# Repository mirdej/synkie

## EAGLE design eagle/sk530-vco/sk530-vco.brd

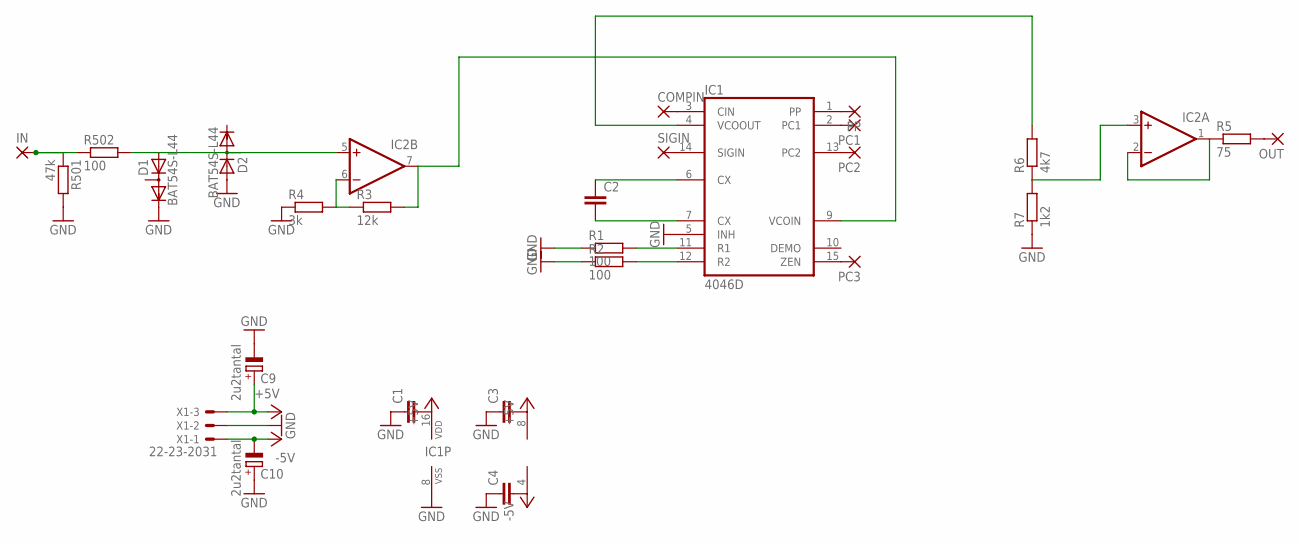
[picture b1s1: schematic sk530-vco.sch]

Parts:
C1, C2, C3, C4: C-EUC1206; C1206
C9, C10: 2u2tantal; CT3528
COMPIN: 3,17/1,1
D1, D2: BAT54S-L44; SOT23
IC1: 4046D; SO16
IC2: DUAL_OPAMPD; SO08
IN: 3,17/1,1
OUT: 3,17/1,1
PC1, PC2, PC3: 3,17/1,1
PP: 3,17/1,1
R1, R2, R502: 100; R1206
R3: 12k; R1206
R4: 3k; R1206
R5: 75; R1206
R6: 4k7; R1206
R7: 1k2; R1206
R501: 47k; R1206
SIGIN: 3,17/1,1
X1: 22-23-2031

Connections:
+5V: C1.2, C3.2, C9.+, IC1.16 (VDD), IC2.8 (V+), X1.3
-5V: C4.2, C10.-, IC2.4 (V-), X1.1
GND: C1.1, C3.1, C4.1, C9.-, C10.+, D1.2 (C), D2.1 (A), IC1.5 (INH), IC1.8 (VSS), R1.1, R2.1, R4.1, R7.1, R501.2, X1.2
unnamed: IC1.2 (PC1), PC1.1
unnamed: OUT.1, R5.2
unnamed: IC1.1 (PP), PP.1
unnamed: IC1.13 (PC2), PC2.1
unnamed: IC1.15 (ZEN), PC3.1
unnamed: IC1.14 (SIGIN), SIGIN.1
unnamed: COMPIN.1, IC1.3 (CIN)
unnamed: C2.1, IC1.6 (CX)
unnamed: C2.2, IC1.7 (CX)
unnamed: IN.1, R501.1, R502.1
unnamed: D1.1 (A), D2.3 (AC), IC2.5 (+IN), R502.2
unnamed: IC1.11 (R1), R1.2
unnamed: IC1.12 (R2), R2.2
unnamed: IC2.6 (-IN), R3.1, R4.2
unnamed: IC1.9 (VCOIN), IC2.7 (OUT), R3.2
unnamed: IC2.1 (OUT), IC2.2 (-IN), R5.1
unnamed: IC1.4 (VCOOUT), R6.2
unnamed: IC2.3 (+IN), R6.1, R7.2

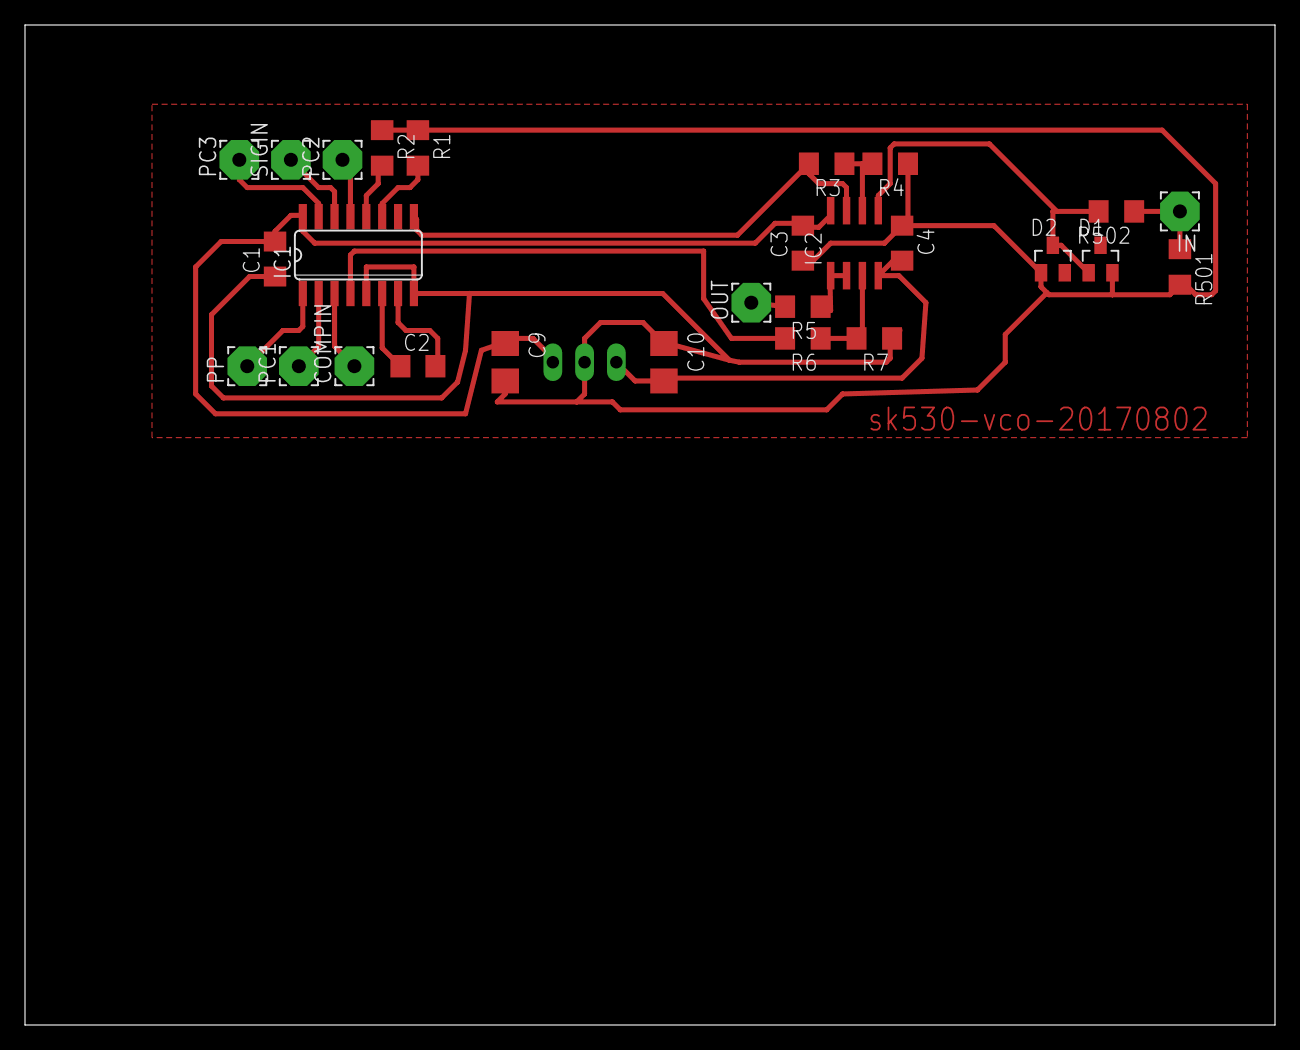
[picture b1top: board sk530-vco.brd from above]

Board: 2 copper layers, 100.0 x 80.0 mm, 28 parts (1 on the bottom side), 21 nets.

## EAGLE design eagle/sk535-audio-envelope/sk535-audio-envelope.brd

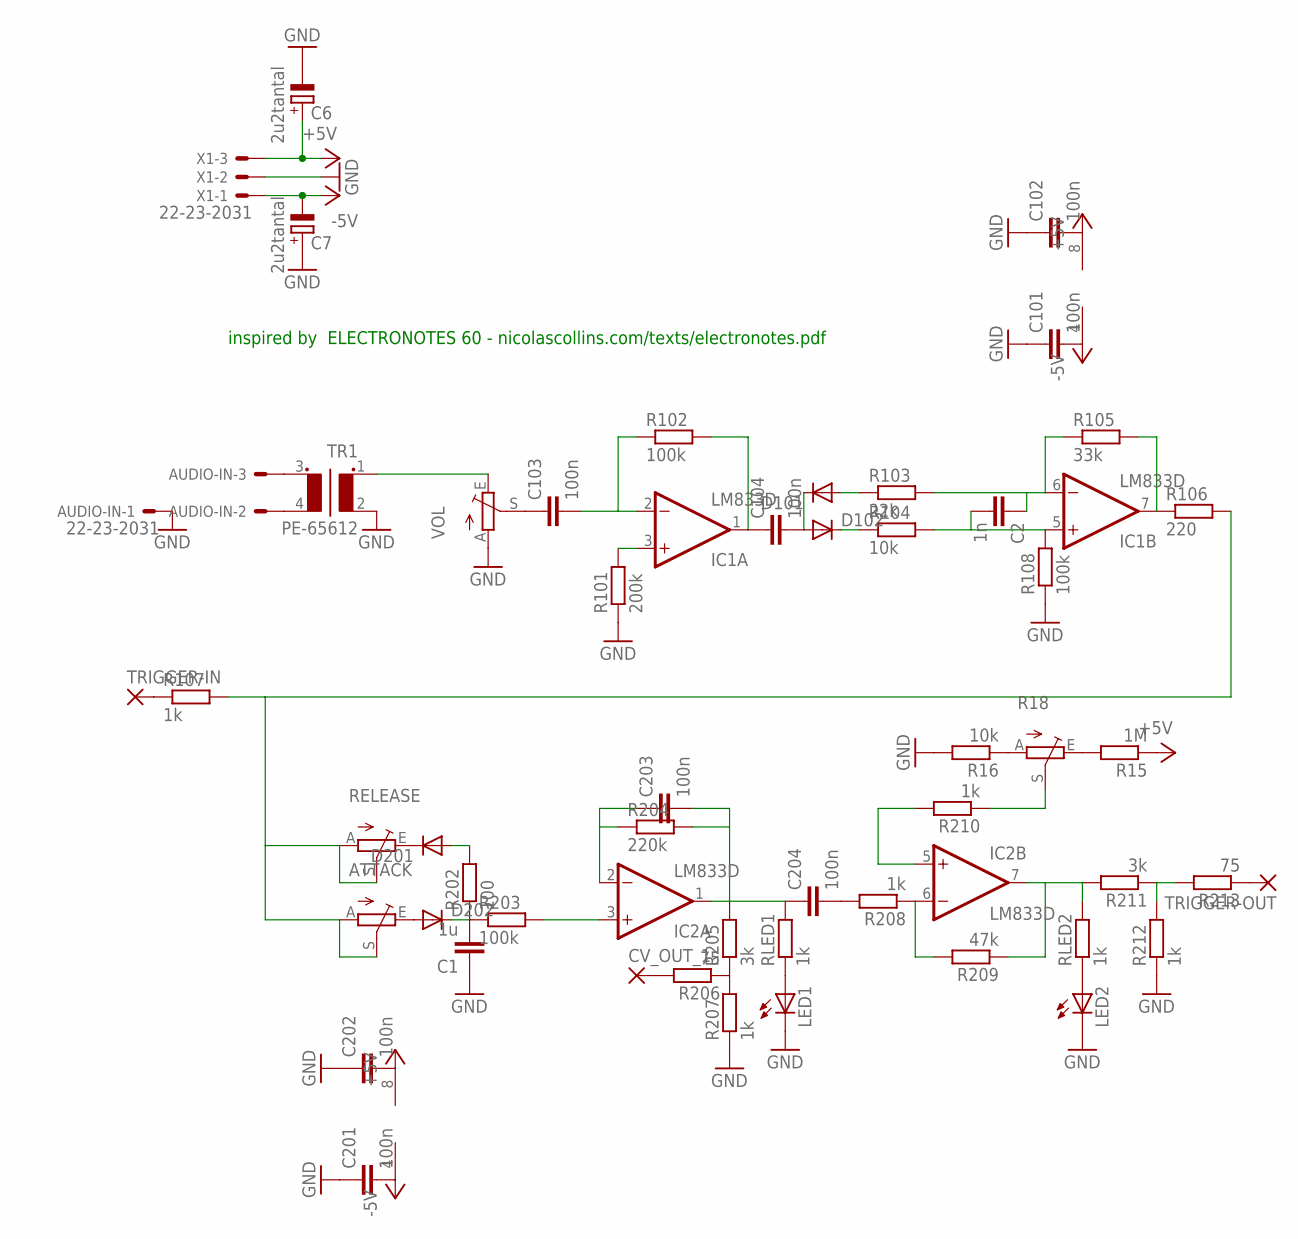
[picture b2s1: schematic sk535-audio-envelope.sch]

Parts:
ATTACK: TRIM_EU-CIP20C-4MM; CIP20C-4MM
AUDIO-IN: 22-23-2031
C1: 1u; C1206
C2: 1n; C1206
C6, C7: 2u2tantal; CT3528
C101, C102, C103, C104, C201, C202, C203, C204: 100n; C1206
CV_OUT_1: 3,17/1,1
D101, D102, D201, D202: DIODE-MINIMELF; MINIMELF
IC1, IC2: LM833D; SO08
LED1, LED2: LED3MM
R15: 1M; R1206
R16, R104: 10k; R1206
R18: TRIM_EU-CIP20C-4MM; CIP20C-4MM
R101: 200k; R1206
R102, R108, R203: 100k; R1206
R103: 22k; R1206
R105: 33k; R1206
R106: 220; R1206
R107, R207, R208, R210, R212: 1k; R1206
R202: 100; R1206
R204: 220k; R1206
R205, R211: 3k; R1206
R206, R213: 75; R1206
R209: 47k; R1206
RELEASE: TRIM_EU-CIP20C-4MM; CIP20C-4MM
RLED1, RLED2: 1k; R1206
TR1: PE-65612
TRIGGER-IN: 3,17/1,1
TRIGGER-OUT: 3,17/1,1
VOL: TRIM_EU-CIP20C-4MM; CIP20C-4MM
X1: 22-23-2031

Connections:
+5V: C6.+, C102.2, C202.2, IC1.8 (V+), IC2.8 (V+), R15.1, X1.3
-5V: C7.-, C101.2, C201.2, IC1.4 (V-), IC2.4 (V-), X1.1
GND: AUDIO-IN.1, C1.1, C6.-, C7.+, C101.1, C102.1, C201.1, C202.1, LED1.K (C), LED2.K (C), R16.2, R101.1, R108.1, R207.1, R212.1, TR1.2, VOL.A, X1.2
unnamed: TR1.1, VOL.E
unnamed: C103.1, VOL.S
unnamed: C103.2, IC1.2 (-IN), R102.1
unnamed: C104.1, IC1.1 (OUT), R102.2
unnamed: IC1.3 (+IN), R101.2
unnamed: C104.2, D101.C, D102.A
unnamed: D102.C, R104.1
unnamed: C2.2, IC1.5 (+IN), R104.2, R108.2
unnamed: C2.1, IC1.6 (-IN), R103.2, R105.1
unnamed: D101.A, R103.1
unnamed: IC1.7 (OUT), R105.2, R106.1
unnamed: R107.1, TRIGGER-IN.1
unnamed: D201.C, RELEASE.E
unnamed: D201.A, R202.2
unnamed: ATTACK.E, D202.A
unnamed: ATTACK.A, ATTACK.S, R106.2, R107.2, RELEASE.A, RELEASE.S
unnamed: C1.2, D202.C, R202.1, R203.1
unnamed: IC2.3 (+IN), R203.2
unnamed: AUDIO-IN.3, TR1.3 (S1)
unnamed: AUDIO-IN.2, TR1.4 (S2)
unnamed: C203.1, IC2.2 (-IN), R204.1
unnamed: C203.2, C204.1, IC2.1 (OUT), R204.2, R205.2, RLED1.2
unnamed: R205.1, R206.1, R207.2
unnamed: LED1.A, RLED1.1
unnamed: C204.2, R208.2
unnamed: IC2.6 (-IN), R208.1, R209.2
unnamed: IC2.7 (OUT), R209.1, R211.2, RLED2.2
unnamed: R15.2, R18.E
unnamed: R16.1, R18.A
unnamed: R18.S, R210.1
unnamed: IC2.5 (+IN), R210.2
unnamed: LED2.A, RLED2.1
unnamed: R213.1, TRIGGER-OUT.1
unnamed: R211.1, R212.2, R213.2
unnamed: CV_OUT_1.1, R206.2

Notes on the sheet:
inspired by ELECTRONOTES 60 - nicolascollins.com/texts/electronotes.pdf

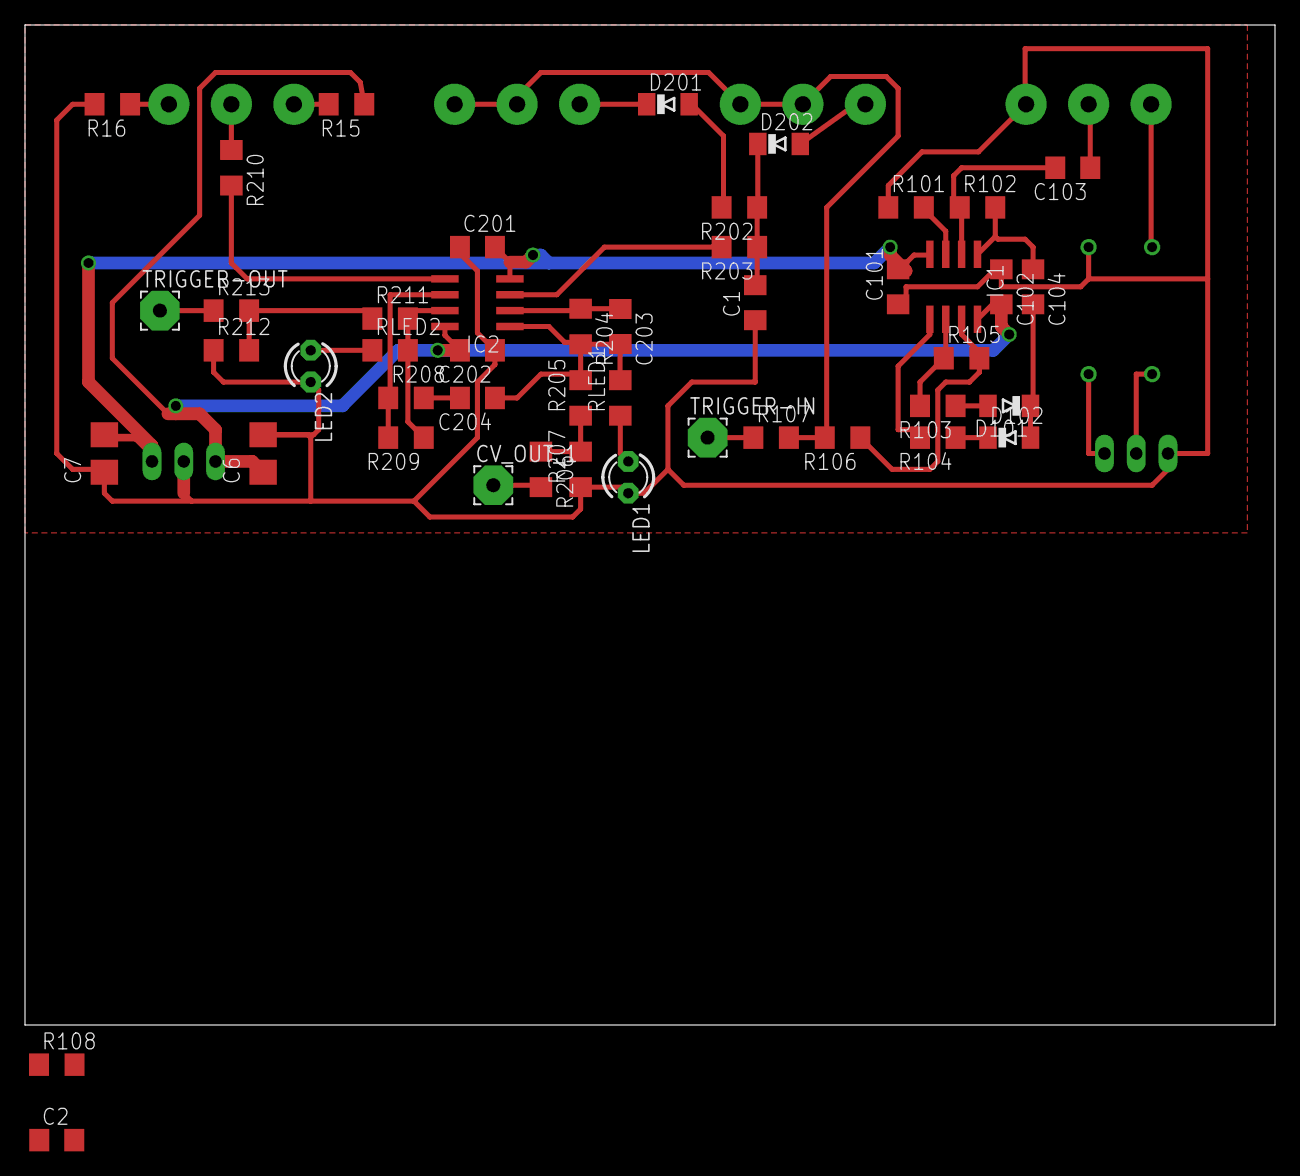
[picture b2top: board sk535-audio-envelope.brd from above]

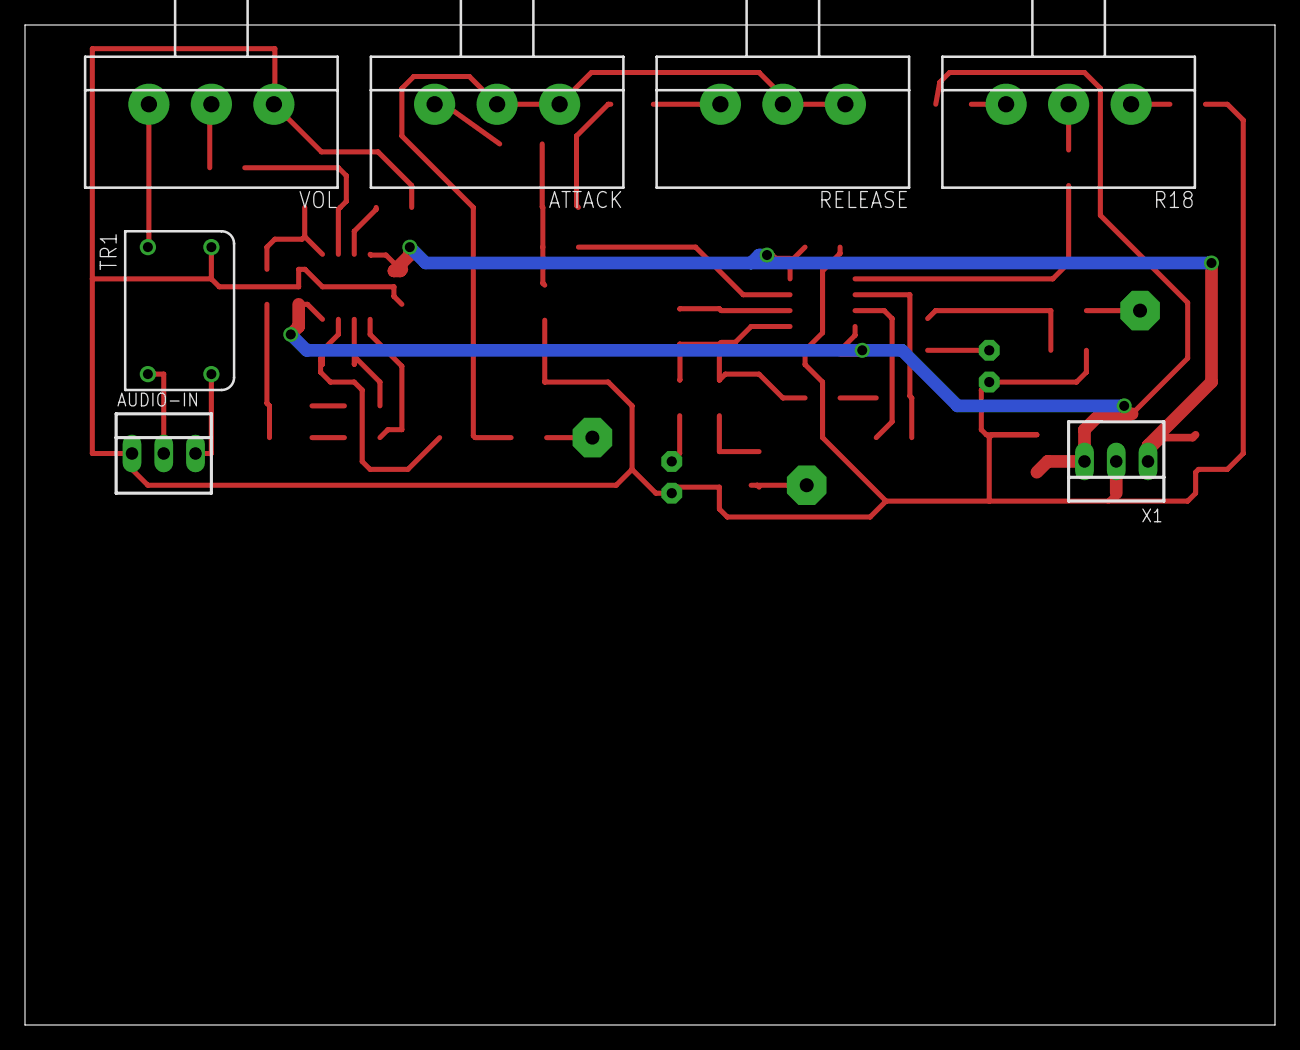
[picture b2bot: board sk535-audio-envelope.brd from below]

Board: 2 copper layers, 100.0 x 80.0 mm, 54 parts (7 on the bottom side), 38 nets.

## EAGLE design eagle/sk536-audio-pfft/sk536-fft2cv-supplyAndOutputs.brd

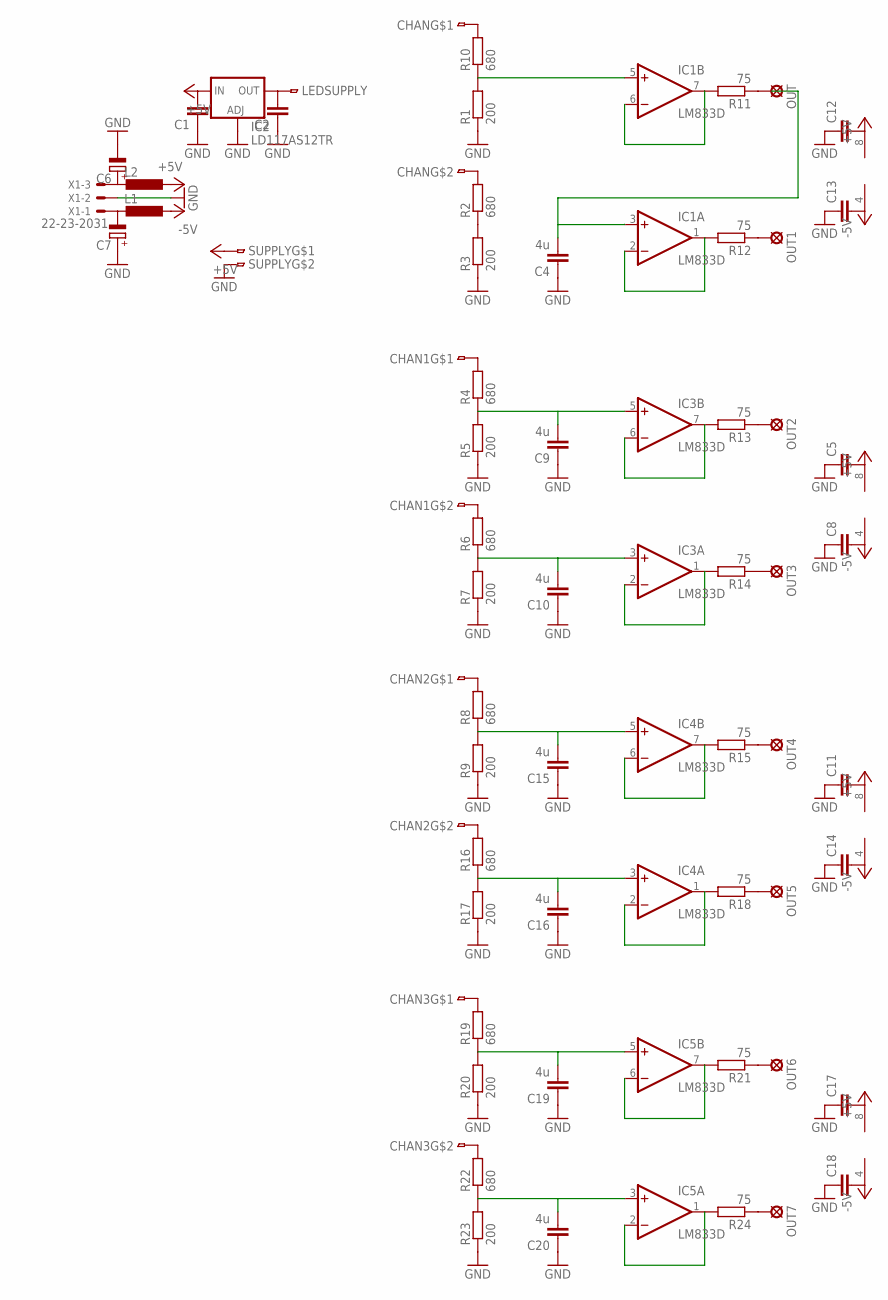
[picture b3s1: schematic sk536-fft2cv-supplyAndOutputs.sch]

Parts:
C1, C2, C5, C8, C11, C12, C13, C14, C17, C18: C-EUC0603; C0603
C4, C9, C10, C15, C16, C19, C20: 4u; C1206
C6, C7: CPOL-EUCT3528; CT3528
CHAN, CHAN1, CHAN2, CHAN3: 2PIN-SMD-2.54
IC1, IC3, IC4, IC5: LM833D; SO08
IC2: LD117AS12TR; SOT223
L1, L2: L-EUL2012C; L2012C
LEDSUPPLY: 1PINSMD
OUT, OUT1, OUT2, OUT3, OUT4, OUT5, OUT6, OUT7: LSP13
R1, R3, R5, R7, R9, R17, R20, R23: 200; R1206
R2, R4, R6, R8, R10, R16, R19, R22: 680; R1206
R11, R12, R13, R14, R15, R18, R21, R24: 75; R1206
SUPPLY: 2PIN-SMD-2.54
X1: 22-23-2031

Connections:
+5V: C1.2, C5.2, C11.2, C12.2, C17.2, IC1.8 (V+), IC2.3 (IN), IC3.8 (V+), IC4.8 (V+), IC5.8 (V+), L2.1, SUPPLY.2
-5V: C8.2, C13.2, C14.2, C18.2, IC1.4 (V-), IC3.4 (V-), IC4.4 (V-), IC5.4 (V-), L1.1
GND: C1.1, C2.1, C4.1, C5.1, C6.-, C7.+, C8.1, C9.1, C10.1, C11.1, C12.1, C13.1, C14.1, C15.1, C16.1, C17.1, C18.1, C19.1, C20.1, IC2.1 (ADJ), R1.1, R3.1, R5.1, R7.1, R9.1, R17.1, R20.1, R23.1, SUPPLY.3, X1.2
unnamed: CHAN.2, R10.2
unnamed: C2.2, IC2.4 (OUT), LEDSUPPLY.2
unnamed: OUT.MP, R11.1
unnamed: IC1.5 (+IN), R1.2, R10.1
unnamed: IC1.6 (-IN), IC1.7 (OUT), R11.2
unnamed: CHAN.3, R2.2
unnamed: C4.2, IC1.3 (+IN)
unnamed: IC1.1 (OUT), IC1.2 (-IN), R12.2
unnamed: OUT1.MP, R12.1
unnamed: CHAN1.2, R4.2
unnamed: C9.2, IC3.5 (+IN), R4.1, R5.2
unnamed: IC3.6 (-IN), IC3.7 (OUT), R13.2
unnamed: OUT2.MP, R13.1
unnamed: C10.2, IC3.3 (+IN), R6.1, R7.2
unnamed: IC3.1 (OUT), IC3.2 (-IN), R14.2
unnamed: CHAN1.3, R6.2
unnamed: OUT3.MP, R14.1
unnamed: CHAN2.2, R8.2
unnamed: C15.2, IC4.5 (+IN), R8.1, R9.2
unnamed: IC4.6 (-IN), IC4.7 (OUT), R15.2
unnamed: OUT4.MP, R15.1
unnamed: C16.2, IC4.3 (+IN), R16.1, R17.2
unnamed: IC4.1 (OUT), IC4.2 (-IN), R18.2
unnamed: CHAN2.3, R16.2
unnamed: OUT5.MP, R18.1
unnamed: CHAN3.2, R19.2
unnamed: C19.2, IC5.5 (+IN), R19.1, R20.2
unnamed: IC5.6 (-IN), IC5.7 (OUT), R21.2
unnamed: OUT6.MP, R21.1
unnamed: C20.2, IC5.3 (+IN), R22.1, R23.2
unnamed: IC5.1 (OUT), IC5.2 (-IN), R24.2
unnamed: CHAN3.3, R22.2
unnamed: OUT7.MP, R24.1
unnamed: R2.1, R3.2
unnamed: C7.-, L1.2, X1.1
unnamed: C6.+, L2.2, X1.3

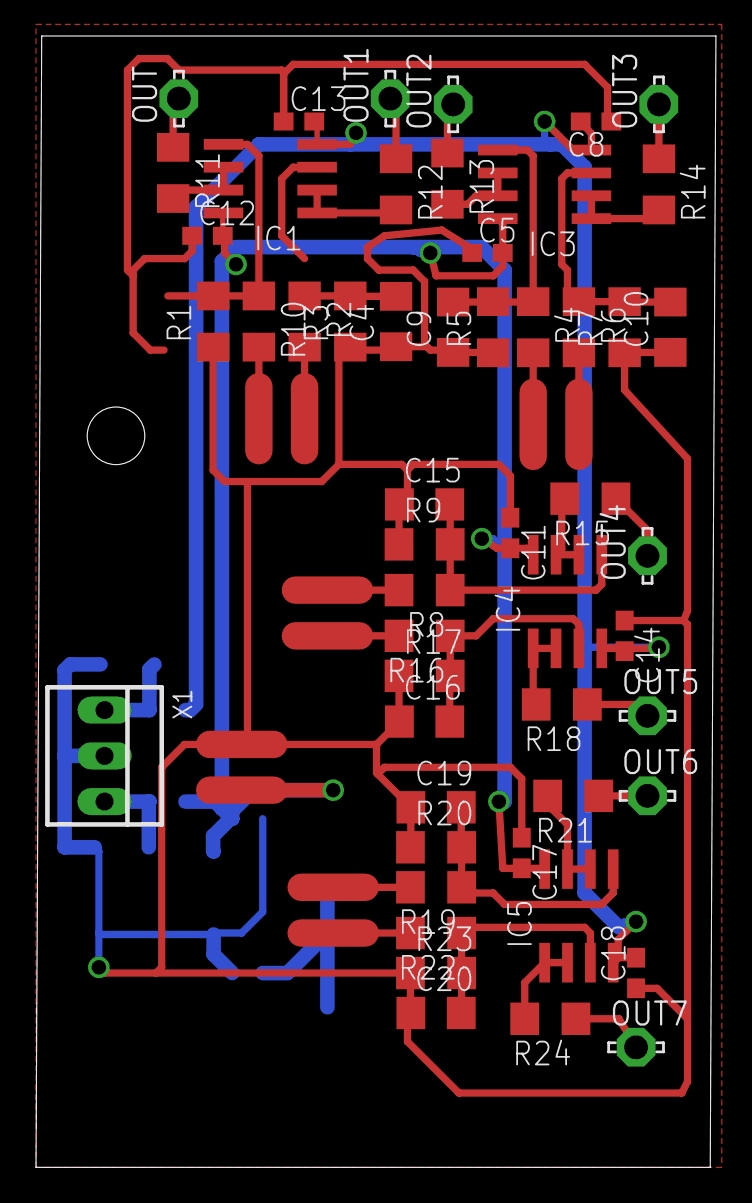
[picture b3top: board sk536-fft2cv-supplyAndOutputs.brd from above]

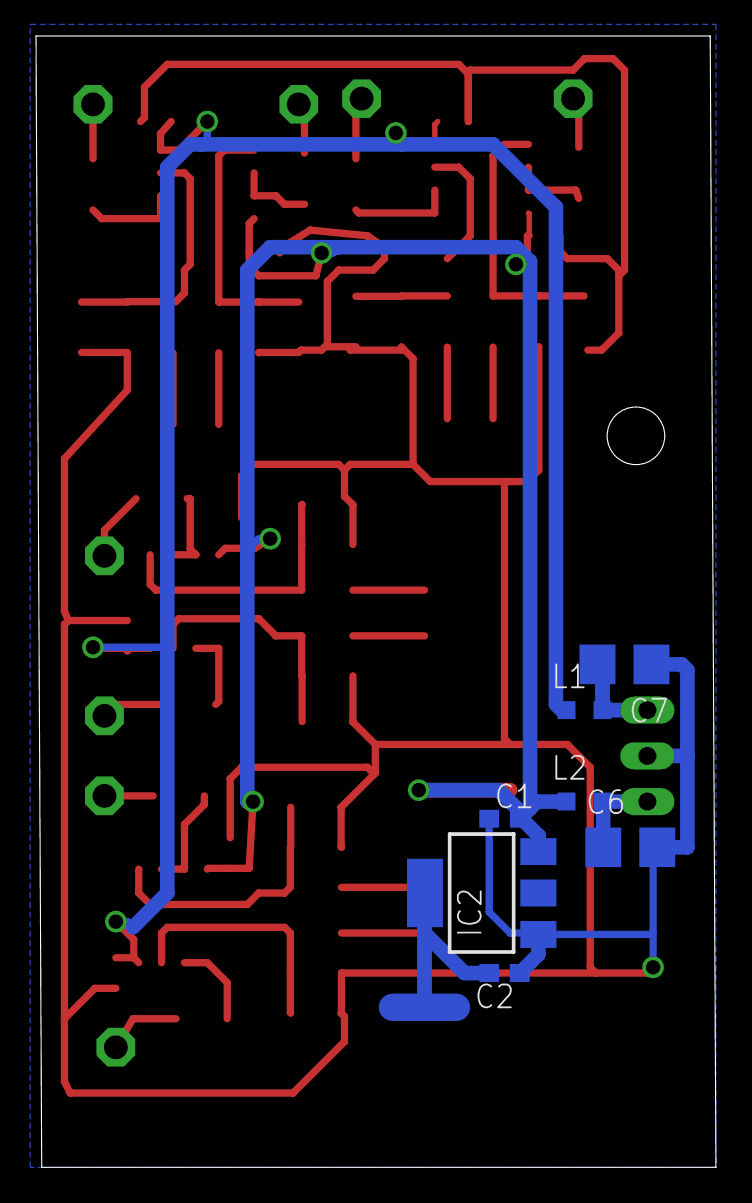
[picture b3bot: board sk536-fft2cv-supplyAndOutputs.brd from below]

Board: 2 copper layers, 37.8 x 62.9 mm, 65 parts (8 on the bottom side), 39 nets.

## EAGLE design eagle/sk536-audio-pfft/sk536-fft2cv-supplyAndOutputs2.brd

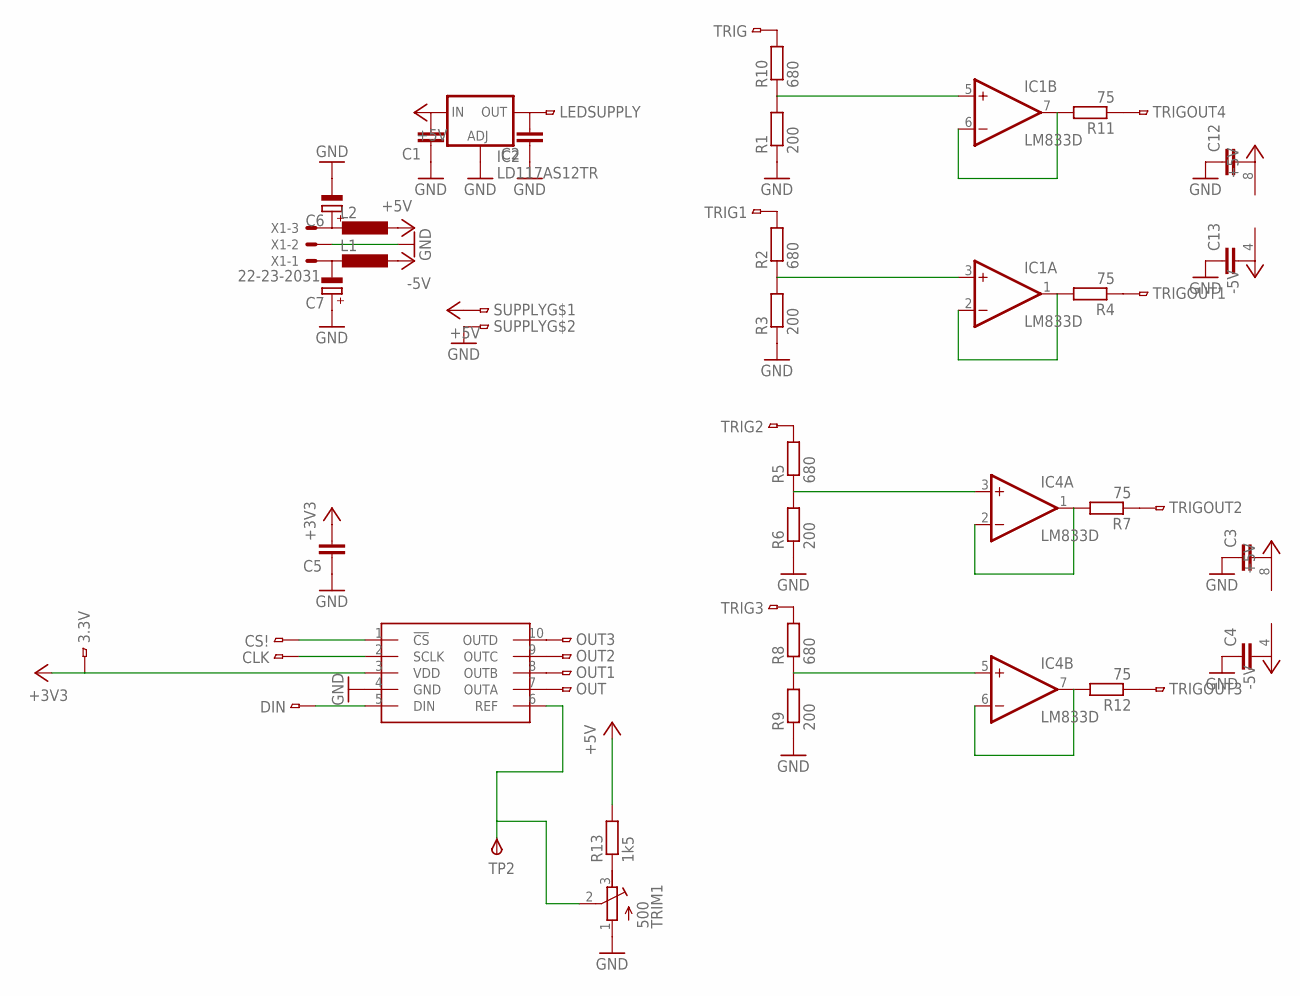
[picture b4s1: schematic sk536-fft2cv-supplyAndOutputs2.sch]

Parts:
3.3V: 1PINSMDSMALL; 1PINSMD-SMALL
C1, C2, C3, C4, C5, C12, C13: C-EUC0603; C0603
C6, C7: CPOL-EUCT3528; CT3528
CLK: 1PINSMDSMALL; 1PINSMD-SMALL
CS!: 1PINSMDSMALL; 1PINSMD-SMALL
DIN: 1PINSMDSMALL; 1PINSMD-SMALL
IC1, IC4: LM833D; SO08
IC2: LD117AS12TR; SOT223
L1, L2: L-EUL2012C; L2012C
LEDSUPPLY: 1PINSMD
OUT, OUT1, OUT2, OUT3: 1PINSMDSMALL; 1PINSMD-SMALL
R1, R3, R6, R9: 200; R1206
R2, R5, R8, R10: 680; R1206
R4, R7, R11, R12: 75; R1206
R13: 1k5; R1206
SUPPLY: 2PIN-SMD-2.54
TP2: TPSB2,54; B2,54
TRIG, TRIG1, TRIG2, TRIG3: 1PINSMDSMALL; 1PINSMD-SMALL
TRIGOUT1, TRIGOUT2, TRIGOUT3, TRIGOUT4: 1PINSMDSMALL; 1PINSMD-SMALL
TRIM1: 500; RTRIM64Y
U$1: MAX5741; UMAX10
X1: 22-23-2031

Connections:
+3V3: 3.3V.P$1, C5.2, U$1.3 (VDD)
+5V: C1.2, C3.2, C12.2, IC1.8 (V+), IC2.3 (IN), IC4.8 (V+), L2.1, R13.2, SUPPLY.2
-5V: C4.2, C13.2, IC1.4 (V-), IC4.4 (V-), L1.1
GND: C1.1, C2.1, C3.1, C4.1, C5.1, C6.-, C7.+, C12.1, C13.1, IC2.1 (ADJ), R1.1, R3.1, R6.1, R9.1, SUPPLY.3, TRIM1.1 (A), U$1.4 (GND), X1.2
unnamed: R10.2, TRIG.P$1
unnamed: C2.2, IC2.4 (OUT), LEDSUPPLY.2
unnamed: R2.2, TRIG1.P$1
unnamed: IC1.5 (+IN), R1.2, R10.1
unnamed: IC1.6 (-IN), IC1.7 (OUT), R11.2
unnamed: R5.2, TRIG2.P$1
unnamed: R8.2, TRIG3.P$1
unnamed: IC1.3 (+IN), R2.1, R3.2
unnamed: IC1.1 (OUT), IC1.2 (-IN), R4.2
unnamed: R11.1, TRIGOUT4.P$1
unnamed: R4.1, TRIGOUT1.P$1
unnamed: R7.1, TRIGOUT2.P$1
unnamed: IC4.3 (+IN), R5.1, R6.2
unnamed: IC4.1 (OUT), IC4.2 (-IN), R7.2
unnamed: R12.1, TRIGOUT3.P$1
unnamed: OUT.P$1, U$1.7 (OUTA)
unnamed: OUT1.P$1, U$1.8 (OUTB)
unnamed: IC4.5 (+IN), R8.1, R9.2
unnamed: IC4.6 (-IN), IC4.7 (OUT), R12.2
unnamed: OUT2.P$1, U$1.9 (OUTC)
unnamed: OUT3.P$1, U$1.10 (OUTD)
unnamed: DIN.P$1, U$1.5 (DIN)
unnamed: R13.1, TRIM1.3 (E)
unnamed: CLK.P$1, U$1.2 (SCLK)
unnamed: CS!.P$1, U$1.1 (!CS)
unnamed: C7.-, L1.2, X1.1
unnamed: C6.+, L2.2, X1.3
unnamed: TP2.TP, TRIM1.2 (S), U$1.6 (REF)

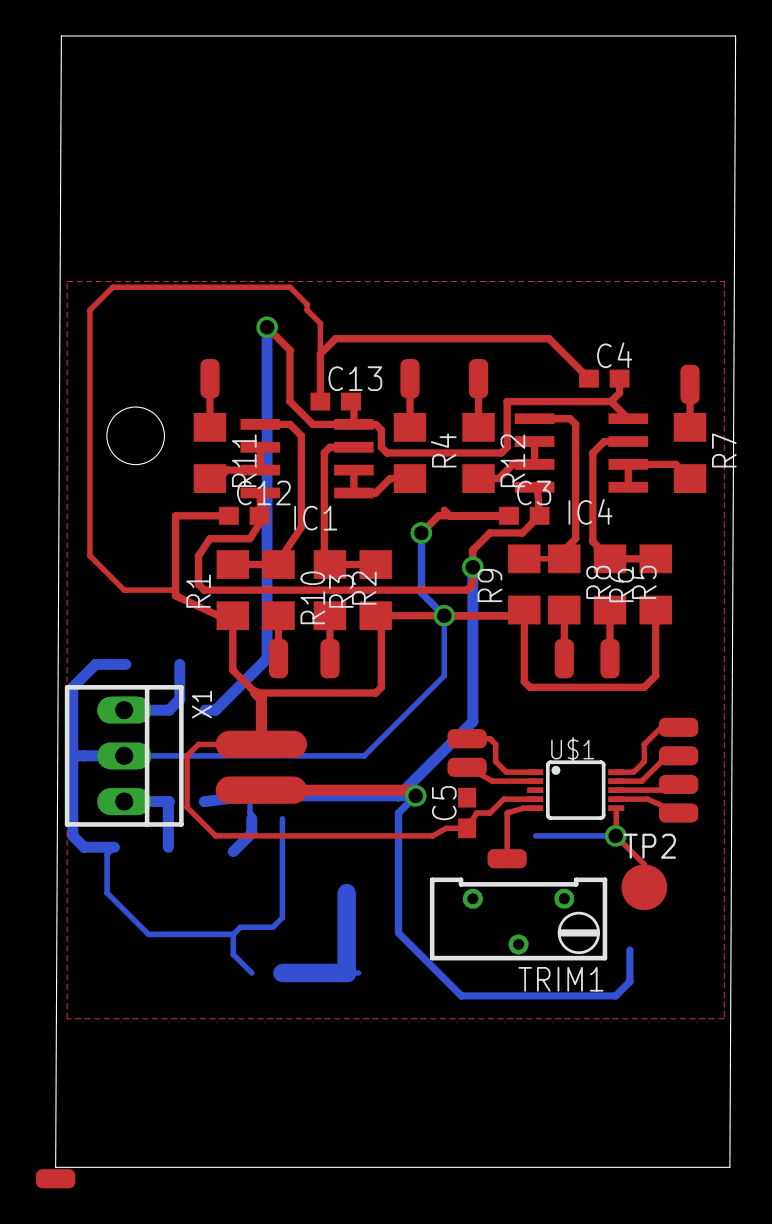
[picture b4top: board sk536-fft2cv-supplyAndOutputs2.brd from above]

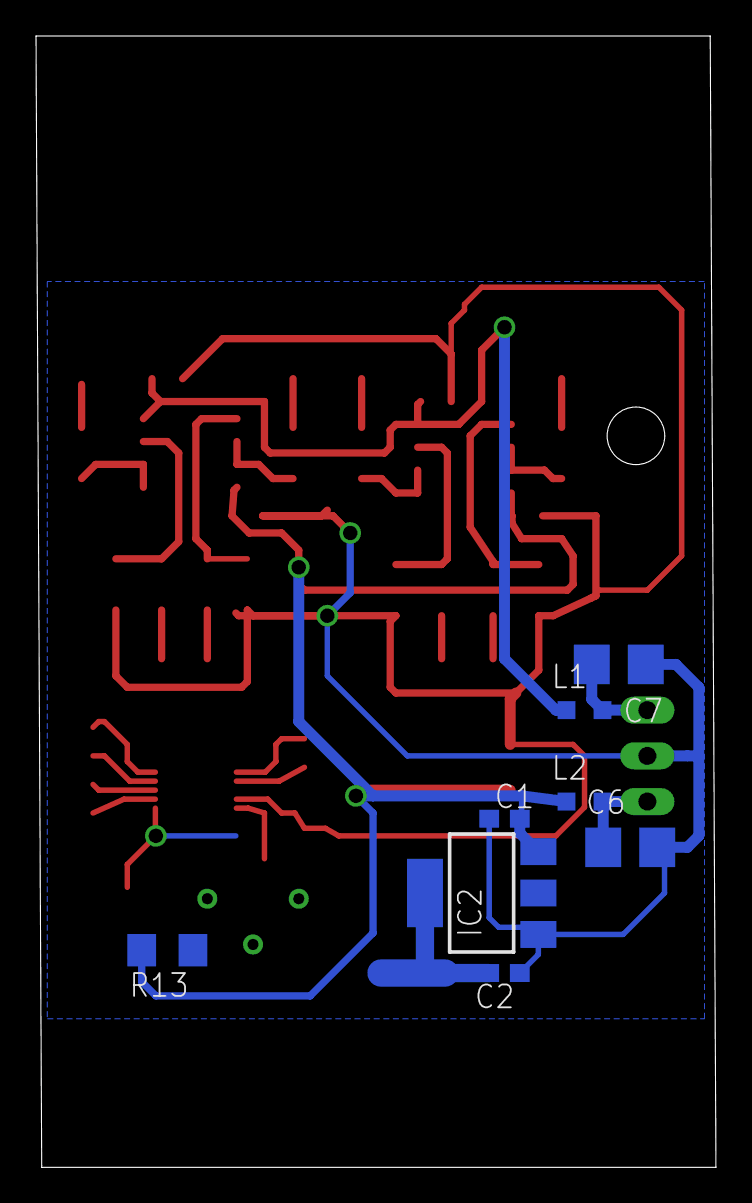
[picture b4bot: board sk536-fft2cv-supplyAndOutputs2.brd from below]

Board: 2 copper layers, 37.8 x 62.9 mm, 49 parts (9 on the bottom side), 32 nets.
